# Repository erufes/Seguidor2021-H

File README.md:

# Seguidor2021-H

Projeto de hardware do robô da equipe de Seguidor de Linha do projeto Equipe de Robótica da UFES (ERUS) para o robô de 2020 e 2021, com objetivo de construir um robô para competir pelas primeiras posições na IronCup 2021 e outras competições afim;

Este projeto é baseado no robô Denstiscalpium Automata, projetado construído pela equipe no ano de 2019, composta por Higor, Lucas Altoe e Breno Odnan.
Link do projeto anterior: https://github.com/Harmonia2Side/Seguidor_IronCup

O projeto usa como base o KiCad, programa open-source de desenvlvimento de circuitos eletrônicos. A versão do programa que o projeto está sendo desenvolvida é 5.1.6.

## Outros links

Site da ERUS: http://www.erus.ufes.br/

Site do projeto de Software: https://github.com/hdogithub/Seguidor2021-S

Site do KiCad: [-]

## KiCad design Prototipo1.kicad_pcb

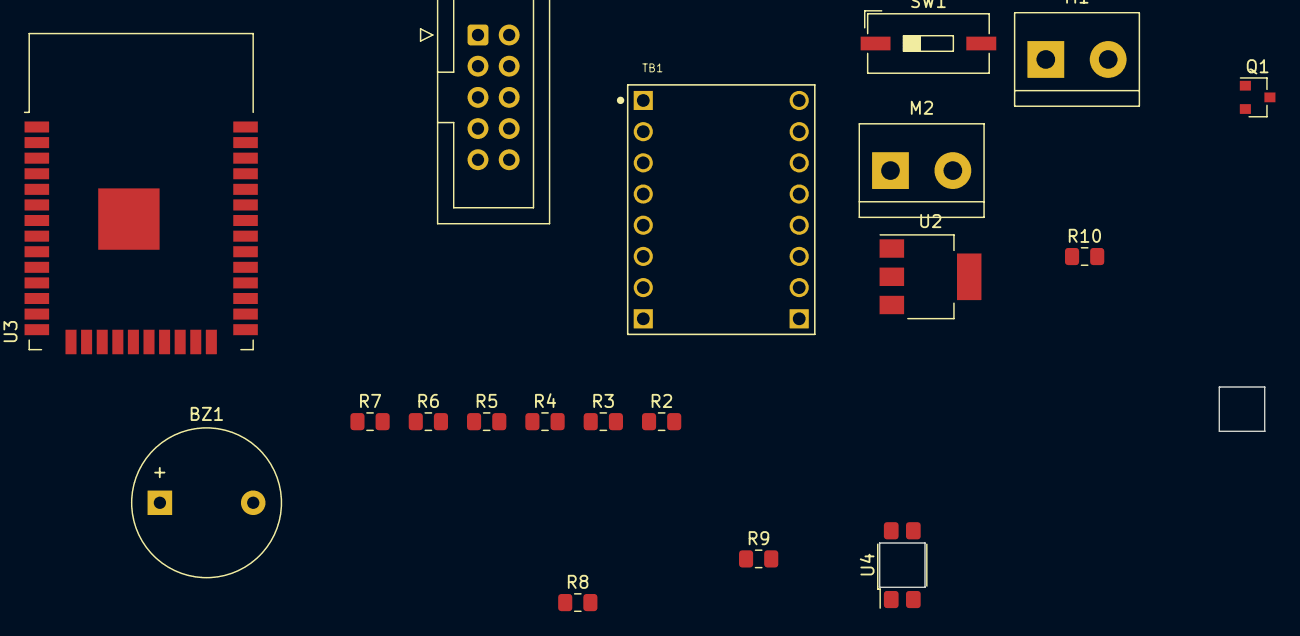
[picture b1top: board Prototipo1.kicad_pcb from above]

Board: 2 copper layers, 20 parts (1 on the bottom side), 10 nets, no tracks yet.

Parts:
BZ1: Buzzer; Buzzer_12x9.5RM7.6
J1: Conn_02x05_Counter_Clockwise; IDC-Header_2x05_P2.54mm_Vertical
M1, M2: Motor_DC; TerminalBlock_bornier-2_P5.08mm
Q1: Q_PMOS_DGS; SOT-23
R2, R3, R4, R5, R6: 220Ω; R_0805_2012Metric_Pad1.15x1.40mm_HandSolder
R7: 2K2Ω; R_0805_2012Metric_Pad1.15x1.40mm_HandSolder
R8: 160; R_0805_2012Metric_Pad1.15x1.40mm_HandSolder
R9: 100K; R_0805_2012Metric_Pad1.15x1.40mm_HandSolder
R10: 43K; R_0805_2012Metric_Pad1.15x1.40mm_HandSolder
SW1: SW_DIP_x01; SW_DIP_SPSTx01_Slide_9.78x4.72mm_W8.61mm_P2.54mm
TB1: POLOLU-713; SHIELD_POLOLU-713
U2: AMS1117-3.3; SOT-223-3_TabPin2
U3: ESP32-WROOM-32
U4, U5: ITR8307; Everlight_ITR8307

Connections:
+3V3: BZ1.1, J1.1, TB1.2, U3.2
/InMosfet: U4.1, U5.1
/OutNivelBateria: R9.2, R10.1
/OutPonteHMotor12: M1.2, TB1.4
/OutPonteHMotor22: M2.2, TB1.6
/Vbat: R9.1, SW1.1, TB1.7
GND: J1.6, Q1.3, R7.2, R10.2, TB1.1, TB1.8, TB1.9, U3.1, U3.15, U3.38, U3.39, U4.4, U5.4
unnamed: BZ1.2, R8.1
unnamed: SW1.2, U2.3
unnamed: Q1.1, R8.2

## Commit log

2020-08-27 Update README.md
    Mudanças iniciais no readme, descrição do projeto e inicio do repositório;
2020-09-06 Adição dos arquivos existentes
    Adição dos arquivos existentes do KiCad
2020-09-06 Adicionado resistor de pull down na ponte H
    Adicionado resistor de pull down no pino enable da ponte H
2020-09-29 Criação inicial do arquivo de PCI e atualização de esquemático
    Criação de um projeto de PCI não finalizado e incompleto, como demonstração de um curso com a Gabrielly. Atualizado o esquemático da ponte H e associado alguns componentes.
2021-11-09 Update README.md
    https://forum.kicad.info/t/warning-avoid-all-links-to-kicad-pcb-org-use-kicad-org/31521
